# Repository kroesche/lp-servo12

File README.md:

12-Servo BoosterPack for Stellaris Launchpad
============================================
by KROESCHE.ORG

---

License
-------
All documentation and design files including schematic and board layout is licensed under a Creative Commons Attribution 3.0 Unported License.

You should have received a copy of the license along with this work.  If not, see <http://creativecommons.org/licenses/by/3.0/>.

Please see the accompanying file LICENSE.TXT.

Summary
-------
This board is designed to be used with a Stellaris Launchpad.  It provides a power supply and connectors for 12 servos.  Each servo control signal can be driven from one half of a Stellaris Wide Timer.  The board is intended to be powered from a 2-cell LiPo battery pack and it will provide a 5-volt supply for the servos and optionally the Launchpad.

Power Supply
------------
The board is intended to be powered from a 2-cell LiPo battery pack or similar and can tolerate an input range of about 6-12V.  The onboard power supply will produce 5 volts with a current up to 5 amps.  The onboard supply can also be used to power the Stellaris Launchpad that is plugged in to the servo board. In order to do this, the jumper JP1 must be shorted.  By leaving this jumper open, you can choose to power the launchpad from a separate supply, either at J10 or through the Launchpad USB connector.

Battery Voltage Measurement
---------------------------
There is a circuit to allow for measurement of the battery supply voltage using the Stellaris A/D convertor.  It uses analog input signal AIN2.  It is scaled so that 6V supply reads 0 and 9V supply reads full scale.

Connectors
----------
* X1 - battery power supply, 6-12 V
* S0A - servo connector, uses wide timer 0A
* S0B - servo connector, uses wide timer 0B
* SnA/B - remaining servo connectors, using wide timer nA/B
* JP1 - short this jumper to supply Launchpad from the onboard supply
* J10 - can supply Launchpad 5V here if JP1 is left open
* J1-J4 - standard Launchpad connectors
* J5 - additional non-standard Launchpad connector needed for wide timer 4

Notes
-----
* If you want to use wide timer 4 (and you will if you want all 12 servos), you will need to add a stake-header connector to your Launchpad in the two holes next to the USB device connector.  You will not be able to use the USB device function if you use wide timer 4 for servo control.

* The board is intended to go under the Launchpad (LP sits on top), but there is no reason that it could not also plug on top of a LP.  It might cover some of the buttons on the top.

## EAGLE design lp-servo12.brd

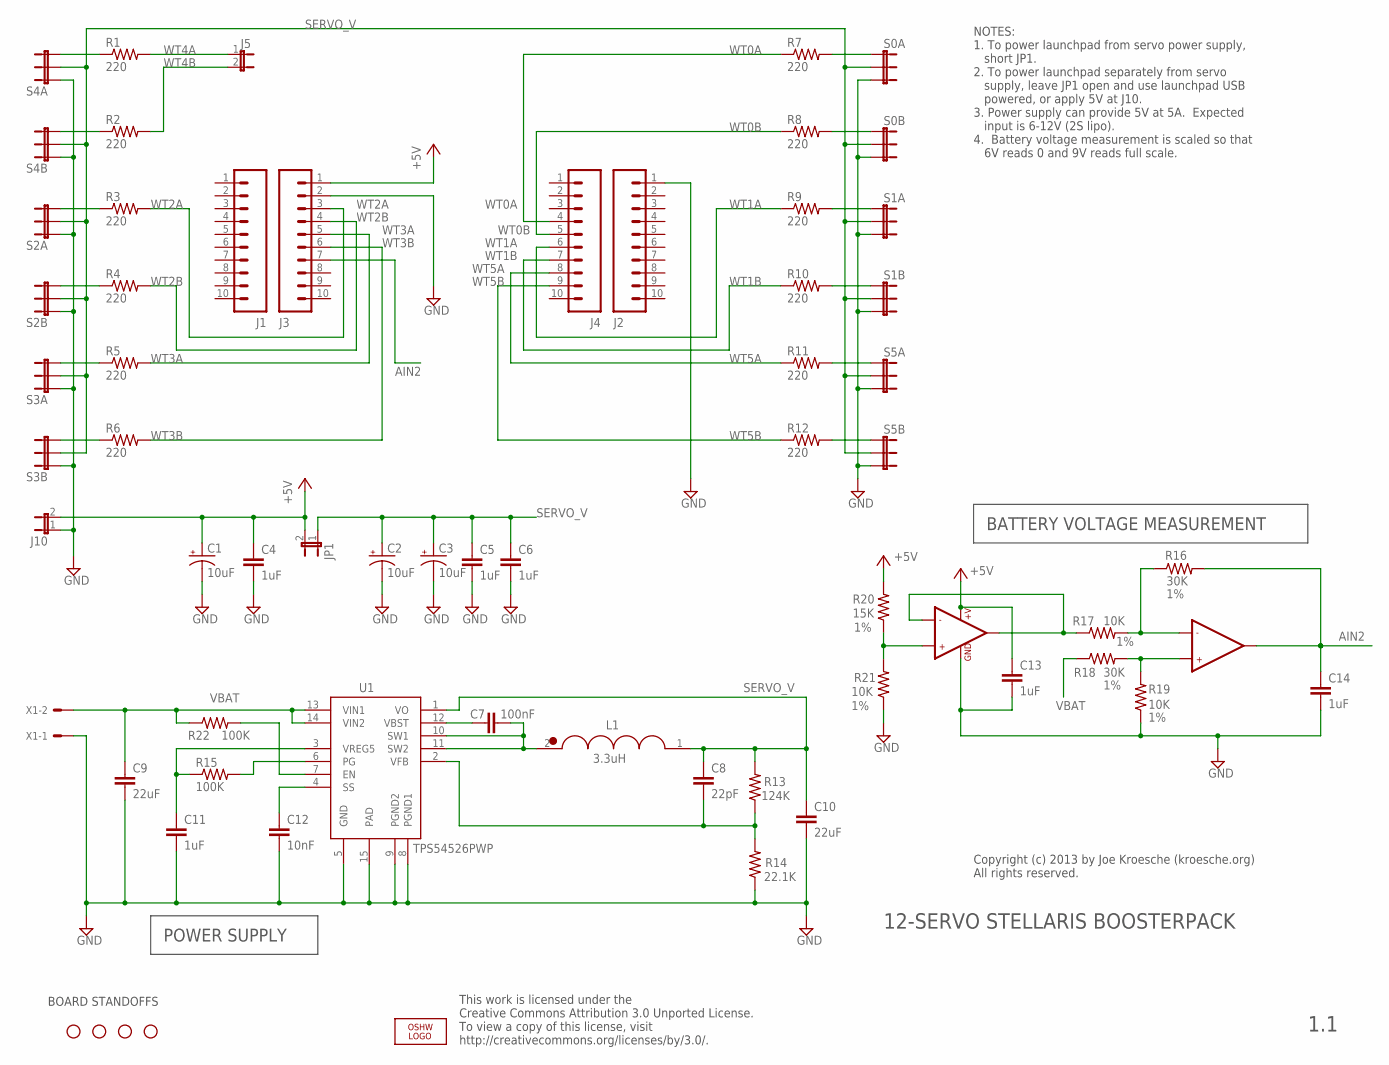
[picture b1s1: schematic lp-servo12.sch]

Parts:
C1, C2, C3: 10uF; EIA3216; PARTNO CAP_10u_20V_20PCT_1206
C4, C5, C6, C11, C13, C14: 1uF; 0805; PARTNO CAP_1u_20V_20PCT_0805
C7: 100nF; 0805; PARTNO CAP_100n_25V_10PCT_0805
C8: 22pF; 0805; PARTNO CAP_22p_50V_10PCT_0805
C9: 22uF; 1210; PARTNO CAP_22u_16V_10PCT_1210
C10: 22uF; 1206; PARTNO CAP_22u_16V_20PCT_1206
C12: 10nF; 0805; PARTNO CAP_10n_50V_10PCT_0805
J1, J2, J3, J4: M10"; 1X10; PARTNO 68002-110HLF
J5: JUMPER-2PTH; 1X02; PARTNO 68002-202HLF
J10: JUMPER-2PTH; 1X02; PARTNO 68016-402
JP1: JUMPER-2PTH; 1X02; PARTNO 68002-202HLF
L1: 3.3uH; VISHAY-IHLP3232DZER; MOUSER# 70-IHLP3232DZER3R3M11
LOGO2: OSHW_LOGO_6MILX0200-NT; OSHW_6X200_NOTEXT
R1: 220; 0805; MOUSER# 667-ERJ-6GEYJ221V
R2, R3, R4, R5, R6, R7, R8, R9, R10, R11, R12: 220; 0805; PARTNO RES_220_20V_10PCT_0805
R13: 124K; 0805; PARTNO RES_124K_20V_1PCT_0805
R14: 22.1K; 0805; PARTNO RES_22.1K_20V_1PCT_0805
R15, R22: 100K; 0805; PARTNO RES_100K_20V_1PCT_0805
R16, R18: 30K; 0805; PARTNO RES_30K_20V_1PCT_0805
R17, R19, R21: 10K; 0805; PARTNO RES_10K_20V_1PCT_0805
R20: 15K; 0805; PARTNO RES_15K_20V_1PCT_0805
S0A, S0B, S1A, S1B, S2A, S2B, S3A, S3B, S4A, S4B, S5A, S5B: JUMPER-3PTH; 1X03; PARTNO 68002-403HLF
STANDOFF1, STANDOFF2, STANDOFF3, STANDOFF4: STAND-OFF
U1: TPS54526PWP; PWP-R-PDSO-G14; PARTNO TPS54526PWP
U2: LMV358; SO08; MOUSER# 595-LMV358QDR
X1: KK-156-2; MOUSER# 538-76650-0208

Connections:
+5V: C1.A (+), C4.1, C13.1, J3.1, J10.2, JP1.2, R20.2, U2.8 (+V)
AIN2: C14.1, J3.7, R16.2, U2.7 (OUT2)
GND: C1.C (-), C2.C (-), C3.C (-), C4.2, C5.2, C6.2, C9.2, C10.2, C11.2, C12.2, C13.2, C14.2, J2.1, J3.2, J10.1, R14.1, R19.1, R21.1, S0A.3, S0B.3, S1A.3, S1B.3, S2A.1, S2B.1, S3A.1, S3B.1, S4A.1, S4B.1, S5A.3, S5B.3, U1.5 (GND), U1.8 (PGND1), U1.9 (PGND2), U1.15 (PAD), U2.4 (GND), X1.1
unnamed: R1.1, S4A.3
unnamed: C7.1, U1.12 (VBST)
unnamed: R2.1, S4B.3
unnamed: R3.1, S2A.3
unnamed: R4.1, S2B.3
unnamed: R5.1, S3A.3
unnamed: C7.2, L1.2 (POS), U1.10 (SW1), U1.11 (SW2)
unnamed: R16.1, R17.2, U2.6 (-IN2)
unnamed: R7.2, S0A.1
unnamed: R6.1, S3B.3
unnamed: R8.2, S0B.1
unnamed: R9.2, S1A.1
unnamed: R10.2, S1B.1
unnamed: R11.2, S5A.1
unnamed: R12.2, S5B.1
unnamed: C8.2, R13.1, R14.2, U1.2 (VFB)
unnamed: R18.2, R19.2, U2.5 (+IN2)
unnamed: R15.2, U1.6 (PG)
unnamed: R22.2, U1.7 (EN)
unnamed: C12.1, U1.4 (SS)
unnamed: R17.1, U2.1 (OUT1), U2.2 (-IN1)
unnamed: C11.1, R15.1, U1.3 (VREG5)
unnamed: R20.1, R21.2, U2.3 (+IN1)
SERVO_V: C2.A (+), C3.A (+), C5.1, C6.1, C8.1, C10.1, JP1.1, L1.1 (NEG), R13.2, S0A.2, S0B.2, S1A.2, S1B.2, S2A.2, S2B.2, S3A.2, S3B.2, S4A.2, S4B.2, S5A.2, S5B.2, U1.1 (VO)
VBAT: C9.1, R18.1, R22.1, U1.13 (VIN1), U1.14 (VIN2), X1.2
WT0A: J4.4, R7.1
WT0B: J4.5, R8.1
WT1A: J4.6, R9.1
WT1B: J4.7, R10.1
WT2A: J3.3, R3.2
WT2B: J3.4, R4.2
WT3A: J3.5, R5.2
WT3B: J3.6, R6.2
WT4A: J5.1, R1.2
WT4B: J5.2, R2.2
WT5A: J4.8, R11.1
WT5B: J4.9, R12.1

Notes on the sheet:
This work is licensed under the Creative Commons Attribution 3.0 Unported License. To view a copy of this license, visit http://creativecommons.org/licenses/by/3.0/.
Copyright (c) 2013 by Joe Kroesche (kroesche.org) All rights reserved.
BOARD STANDOFFS
BATTERY VOLTAGE MEASUREMENT
POWER SUPPLY
12-SERVO STELLARIS BOOSTERPACK
NOTES: 1. To power launchpad from servo power supply, short JP1. 2. To power launchpad separately from servo supply, leave JP1 open and use launchpad USB powered, or apply 5V at J10. 3. Power supply can provide 5V at 5A. Expected input is 6-12V (2S lipo). 4. Battery voltage measurement is scaled so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
1.1

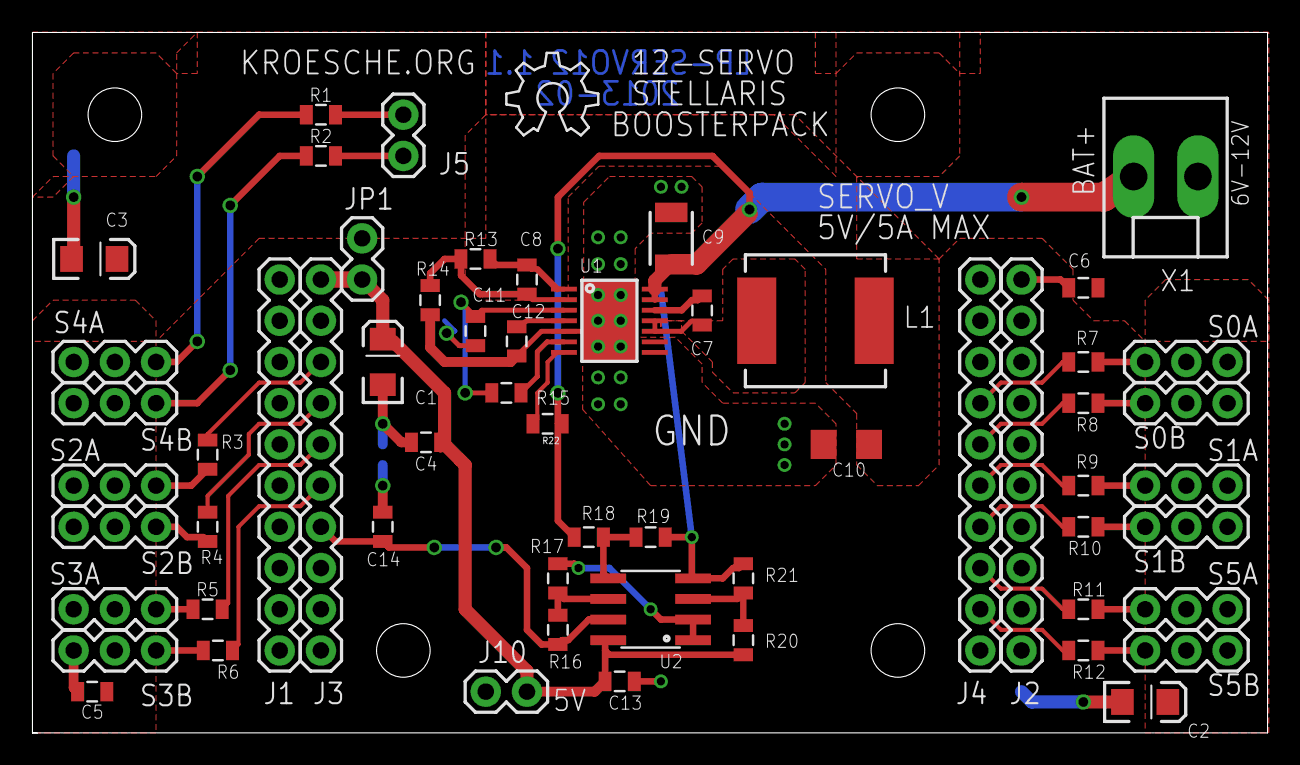
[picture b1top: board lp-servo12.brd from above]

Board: 2 copper layers, 76.1 x 43.2 mm, 64 parts (0 on the bottom side), 40 nets.

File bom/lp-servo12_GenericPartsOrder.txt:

Mfg Part Num	Mfg Name	VID	Vendor Part Num	Description	Customer Ref	Qty-1	Qty-5	Qty-25	Part References	Value
68002-110HLF	FCI	ME	649-68002-110HLF	Header, 0.1in, 10 pos, thru-hole	*	4	20	100	"J1, J2, J3, J4"	
68002-202HLF	FCI	ME	649-68002-202HLF	Header, 0.1in, 2 pos, thru-hole	*	2	10	50	"J5, JP1"	
68002-403HLF	FCI	ME	649-68002-403HLF	Header, 0.1in, 3 pos, thru-hole	*	12	60	300	"S0A, S0B, S1A, S1B, S2A, S2B, S3A, S3B, S4A, S4B, S5A, S5B"	
68016-402	FCI	ME	649-68016-402	Header, 0.1in, 2 pos, thru-hole, right-angle	*	1	5	25	"J10"	
KK-156-2-LOCK-RTANGLE	Molex	ME	538-26-61-5020	Molex, KK .156, Rt ang, 2-pin, lock (0026615020)	*	1	5	25	"X1"	
CAP_1u_20V_20PCT_0805	Murata	ME	81-GRM21BR71E105KA9K	Capacitor, 1uF, ceramic, 10%, 25V, 0805, X7R	*	6	30	150	"C4, C5, C6, C11, C13, C14"	1uF
IHLP3232DZER3R3M11	Vishay Dale	ME	70-IHLP3232DZER3R3M11	Inductor, 3.3uH, 20%, high current, low profile, 9.7A, 14.9mohm	*	1	5	25	"L1"	3.3uH
RES_10K_20V_1PCT_0805	Bourns	ME	652-CR0805FX-1002ELF	Resistor, 10K, 1%, 150V, 1/8W, 0805	*	3	15	75	"R17, R19, R21"	10K
CAP_10n_50V_10PCT_0805	Kemet	ME	80-C0805C103K5R	Capacitor, 10nF, 10%, 50V, 0805, X7R	*	1	5	25	"C12"	10nF
CAP_10u_20V_20PCT_1206	TDK	ME	810-C3216X7R1V106M	Capacitor, 10uF, ceramic, 20%, 35V, 1206, X7R	*	3	15	75	"C1, C2, C3"	10uF
RES_15K_20V_1PCT_0805	Bourns	ME	652-CR0805-FX1502ELF	Resistor, 15K, 1%, 150V, 1/8W, 0805	*	1	5	25	"R20"	15K
RES_22.1K_20V_1PCT_0805	Vishay Dale	ME	71-CRCW0805-22.1K-E3	Resistor, 22.1K, 1%, 150V, 1/8W, 0805	*	1	5	25	"R14"	22.1K
CAP_22p_50V_10PCT_0805	Kemet	ME	80-C0805C220J5G	Capacitor, 22pF, ceramic, 5%, 50V, 0805, C0G(NP0)	*	1	5	25	"C8"	22pF
CAP_22u_16V_10PCT_1210	Taiyo Yuden	ME	963-TMK325BJ226KM-T	Capacitor, 22uF, ceramic, 10%, 25V, 1210, X5R	*	1	5	25	"C9"	22uF
CAP_22u_16V_20PCT_1206	Murata	ME	81-GRM31CR61C226ME5L	Capacitor, 22uF, ceramic, 20%, 16V, 1206, X5R	*	1	5	25	"C10"	22uF
RES_30K_20V_1PCT_0805	Bourns	ME	652-CR0805FX-3002ELF	Resistor, 30K, 1%, 150V, 1/8W, 0805	*	2	10	50	"R16, R18"	30K
RES_100K_20V_1PCT_0805	Vishay Dale	ME	71-CRCW0805-100K-E3	Resistor, 100K, 1%, 150V, 1/8W, 0805	*	1	5	25	"R15"	100K
CAP_100n_25V_10PCT_0805	AVX	ME	581-08053C104K	Capacitor, 100nF, ceramic, 10%, 25V, 0805, X7R	*	1	5	25	"C7"	100nF
RES_124K_20V_1PCT_0805	Vishay Dale	ME	71-CRCW0805124KFKEA	Resistor, 124K, 1%, 150V, 1/8W, 0805	*	1	5	25	"R13"	124K
RES_220_20V_10PCT_0805	Panasonic	ME	667ERJ-6GEYJ221V	Resistor, 220ohms, 5%, 150V, 1/8W, 0805	*	12	60	300	"R1, R2, R3, R4, R5, R6, R7, R8, R9, R10, R11, R12"	220
LMV358QDR	Texas Instruments	ME	595-LMV358QDR	Dual op-amp, low voltage, rail-to-rail	*	1	5	25	"U2"	LMV358
TPS54526PWP	Texas Instruments	ME	595-TPS54526PWP	DC/DC Switching Converter	*	1	5	25	"U1"	TPS54526PWP

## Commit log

2013-01-08 Initial commit of launchpad 12-servo board. This one seems complete and passes (most) design checks. (passes at batchpcb, some minor issues with freedfm)
2013-01-08 Added .gitignore
2013-01-08 Updated .gitignore
2013-01-08 Deleted the custom library since I put it in a common location. Renamed the source files to match the project name.
2013-01-09 Close to final design. Board appears to pass all checks at batchpcb and OSHPark. May need a few more tweaks but really close to being done. The schematic could use some cleaning up for cosmetics. Add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
2013-01-09 Still learning git. All my files were not in the last commit.
2013-01-09 Minor changes to layout. Moved battery connector so that mounting hole can go in the corner. Added notes to the bottom silkscreen.
2013-01-10 Changed notes on back of board from one note with multiple lines to a separate text object for each line. This is because oshpark does not seem to handle multi-line text objects.
2013-01-12 Updated schematic part attributes so that bom-ex script can be used to generate a BOM. Added parts database used and generated bom files (in bom/).
2013-01-22 Added copyright and license text to board and schematic. Cosmetic changes only, no electrical or layout changes. Cleaned up schematic, added some comments. Change LICENSE to use creative commons attr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
2013-01-22 Fixed some resistor values on the voltage measuring op-amp circuit. The orginal values were not correct for a 2S battery (they were for a 1S battery). Updated the bom files to reflect the changes in 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
2013-02-16 Fixed missing pullup on enable line and unconnectd trace on feeback signal for power supply. Those were the two known bugs. Also moved one of the moounting holes and moved the power connector around 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
2013-02-16 Updated generated BOM for revised board. The only change was increasing quantity of 100K resistor.
2013-02-16 Fixed Mouser part number for inductor. Edited generated files instead of re-exporting from eagle.
2013-02-25 Added build bom files, mainly for use in TI launchpad contest. This file shows all mouser part ordering info including qty-1 and qty-1000 pricing.
2013-02-25 Fixed battery voltage mistake text in README
2013-06-12 Added schematic PDF so it is easy to view schematic without needing Eagle.

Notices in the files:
parts and their libraries:
SparkFun-Resistors: Licensing: CC v3.0 Share-Alike You are welcome to use this library for commercial purposes.
